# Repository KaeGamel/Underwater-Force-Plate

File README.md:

# Kaelyn-Gamel
Underwater Force Plate 

Hello all! 

Welcome to the DIY Underwater/Terrestrial Force plate! 

In order to create your own force plate we will be using different platforms and integrating them to gather small forces terrestrially or underwater(can detect .5grams)!

I would start with the files parts and programs needed. I also have attached a word doc that allows you to click on the links for most of the parts to purchase.

Fusion 360 to design the force sensors, Formlab to 3D print.

Matlab to gather data from a NIDAQ that gathers an anolog input from an INA 125P amplifier and Load cell.

EAGLE CAD to generate our circuit (if you want to edit and personalize to your likings)

Most importantly the checklist needed to integrate everything!

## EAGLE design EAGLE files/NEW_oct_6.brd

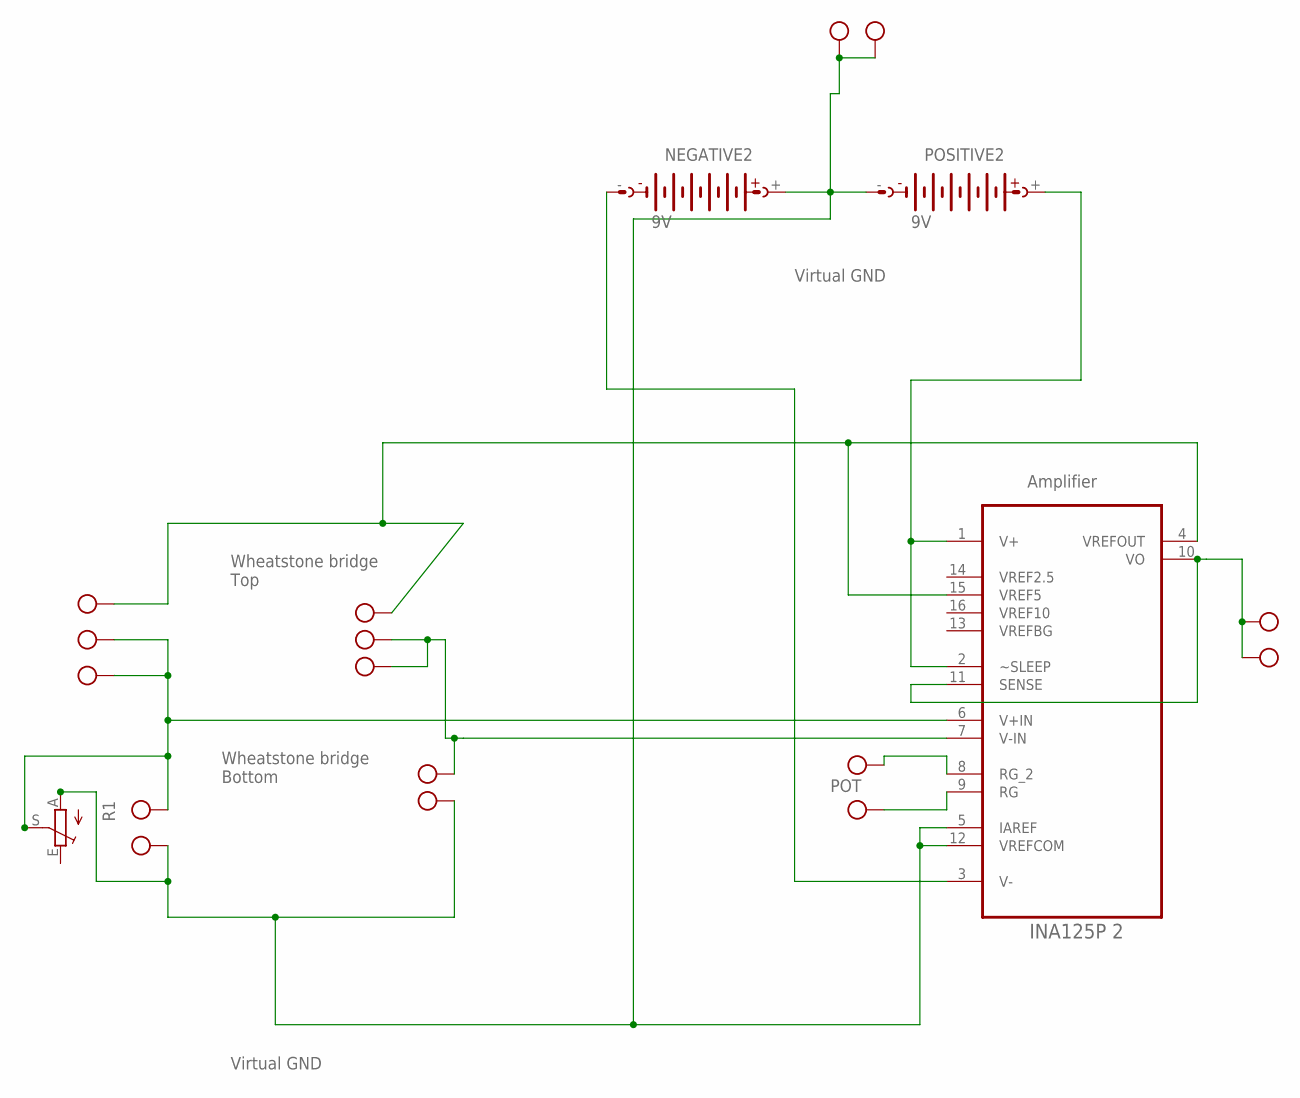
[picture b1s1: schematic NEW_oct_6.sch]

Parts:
FOURTH2, FOURTH5, FOURTH8: W237-102
NEGATIVE2: AB9V
POSITIVE2: AB9V
POT2: W237-102
R1: TRIM_EU-CT6; CT6
SECOND2: W237-102
U3: INA125P 2; DIP254P762X508-16
X1, X2: W237-103

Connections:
unnamed: R1.S, SECOND2.1, U3.6 (V+IN), X1.2, X1.3
unnamed: FOURTH2.2, U3.7 (V-IN), X2.1, X2.2
unnamed: U3.4 (VREFOUT), U3.15 (VREF5), X1.1, X2.3
unnamed: POSITIVE2.+, U3.1 (V+), U3.2 (~SLEEP)
unnamed: NEGATIVE2.-, U3.3 (V-)
unnamed: POT2.2, U3.9 (RG)
unnamed: POT2.1, U3.8 (RG_2)
unnamed: FOURTH5.1, FOURTH5.2, U3.10 (VO), U3.11 (SENSE)
unnamed: FOURTH2.1, FOURTH8.1, FOURTH8.2, NEGATIVE2.+, POSITIVE2.-, R1.A, SECOND2.2, U3.5 (IAREF), U3.12 (VREFCOM)
VREF2.5: U3.14 (VREF2.5)
VREF10: U3.16 (VREF10)
VREFBG: U3.13 (VREFBG)

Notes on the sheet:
Virtual GND
Wheatstone bridge Top
Wheatstone bridge Bottom
POT
Amplifier

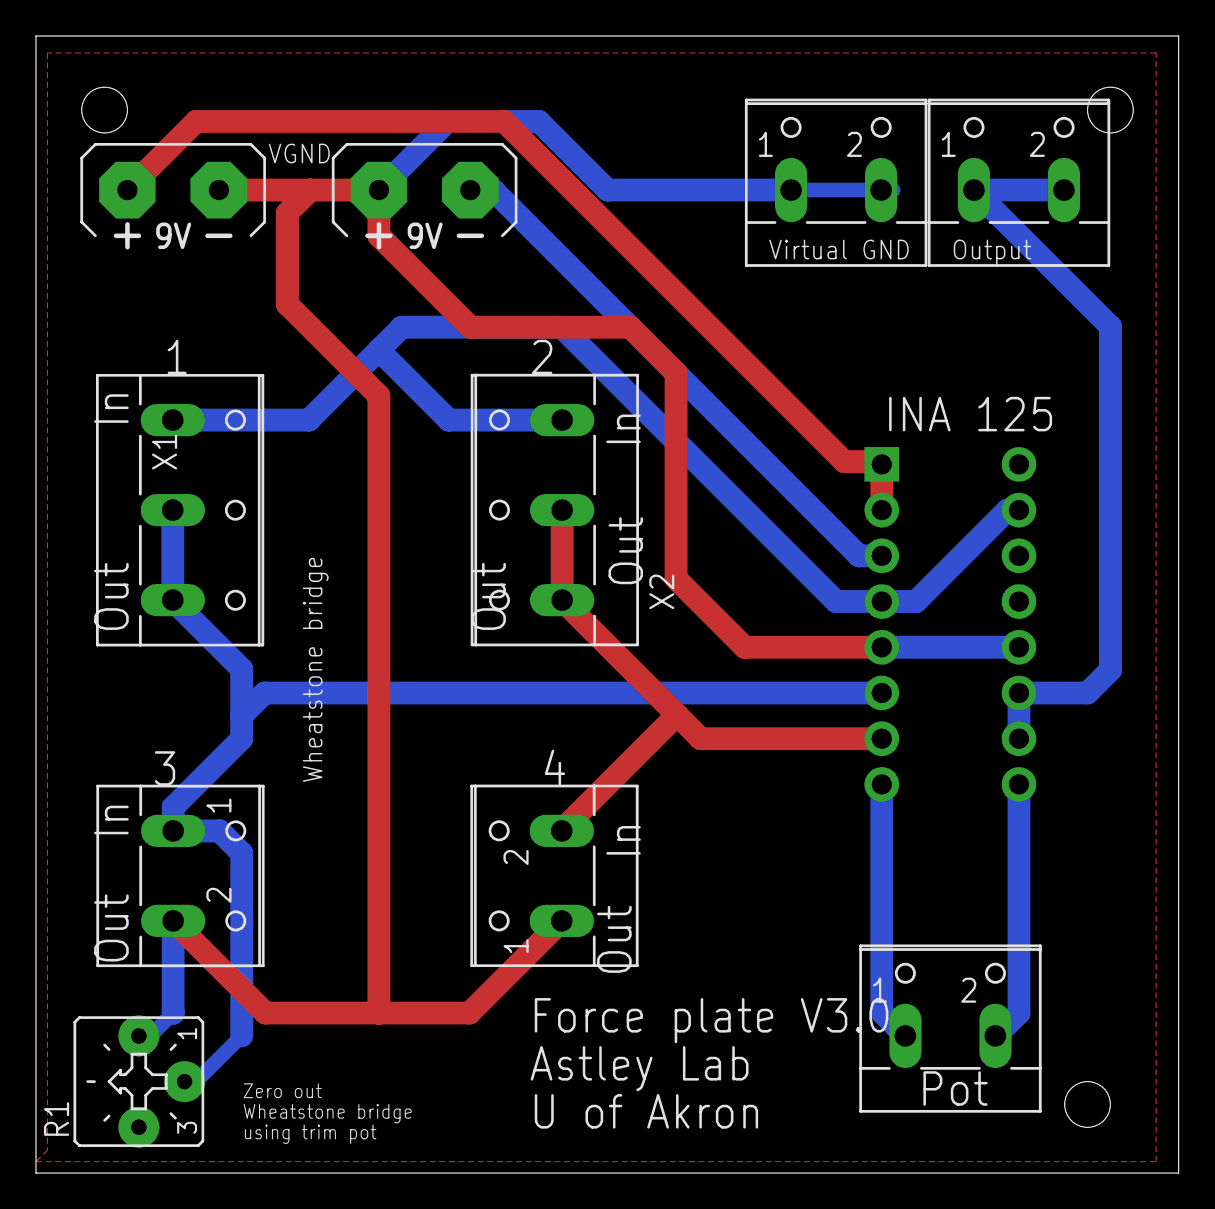
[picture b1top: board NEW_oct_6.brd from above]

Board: 2 copper layers, 63.5 x 63.2 mm, 11 parts (0 on the bottom side), 9 nets.

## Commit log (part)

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2021-07-15 Create Interacting with load Sensors and NIDAQ
2021-09-01 Corner 1 and corner 2 Fusion 360 file
2021-09-01 Heavily Referenced Papers
2021-09-01 Stl File
2021-09-01 Circuit design
2021-10-21 CD added code
    Added new matlab calibration code for easier clicking :)
2021-10-21 Added gather data code V2
    For two vertical channels
2021-10-26 added user feedback for zeroing force
    you can now pick if it was vertical, fore-aft, or horizontal
2021-10-26 Added Calibration Matrix calculator for Matlab
2021-11-05 Drift correction! :)
2021-11-24 added code for syncing force with video
2021-12-14 Fixed video sync code
2022-01-18 Added code to sync kinematics data
2022-02-18 added comments and fixed save lines
2022-02-18 added abc_angle to calculate limb angles
2022-02-22 updated a bunch of save stuff
2022-02-23 added comments and save row
2022-04-28 For Plotting
2022-05-03 Add kinematics variables to force code
2022-05-25 Added plotting for 3+ y-axis
2022-06-01 Circuit Board Schematic
    INA 125P Schematic to amplify a custom Load cell using strain gauges in a Wheatstone bridge configuration
2022-06-02 Update create calibration matrice.py
    ### No words allowed in the Excel file:
    ## these numbers come from running the data file in matlab adding and removing weight
    ## THEN running calibration code clicking the get pts and then extracting the number spit out for each specific weight
    ## here is an example that will spit out a calibration matrix
    ## Vert Voltage, Fore-aft Voltage, Lateral voltage, Actual weight placed Vertically, Actual weight placed foreaft, Actual weight placed lateral
    ### EX. .508 , .02, .03, 5 grams, 0 grams, 0 grams
2023-01-25 STEP File 3D load cells
2023-05-17 Add files via upload
    Added a MATLAB version of the code to find a calibration matrix
2026-02-24 Gerber Files
    Gerber Files for Newer Circuit Printing (e.g. JLCPCB)
2026-02-24 Rename ForceAmplFiles.zip to GerberFiles.zip
2026-03-04 Create PyDAQ.py
    Uploading Jacob's Python Code for Acquiring NIDAQ data
